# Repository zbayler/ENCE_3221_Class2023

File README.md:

# Kitchen Timer
Embedded Systems Programming;  
University of Denver, ENCE 3231

### Phase A: (guided)  
Designing and building a kitchen timer Arduino shield. 
- PCB design (but used provided physical version for the sake of time)
- Code development

### Phase B:  
Designing and building a kitchen timer.  
- Standalone PCB  
- 3D printing an enclosure

### Phase C: (incomplete)
STM32F407 Discovery Kit kitchen timer implementation. 

### Phase D: (all files included in separate folder) 
Final Project - Mini Lightsaber

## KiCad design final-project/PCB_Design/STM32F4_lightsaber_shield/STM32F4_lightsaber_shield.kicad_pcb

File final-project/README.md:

# Mini Lightsaber
Embedded Systems Programming;  
University of Denver, ENCE 3231

### Project Idea: 
Build a mini lightsaber using an IMU, LED, and speaker

### Project Requirements: 
- Design a PCB shield for the STM32F407G Discovery Board 
- Build and test a prototype circuit

### Components included: 
- GY-521 Inertial Measurement Unit
- 4 pin RGB LED
- Speaker (connected with aux cord) 
- USB to microUSB adapter

### Folder Structure: 
- Audio Files: lightsaber .wav files 
- Blad Design: designs for the mini blade 
- Hardware Documents: datasheets and other documentation 
- Notes: pictures, videos, presentations, etc. 
- PCB Design: the kiCAD folder as well as gerber, schematics, BOM, etc. 
- STM32 Code: all programs used to test components and build the system 

### Status/Summary:   
Followed "Mutex Embedded" tutorials on youtube to help set up the IMU and play audio files.
IMU and LED test were successful and were successfully tested together (video in notes).
No luck playing an audio file from the USB drive and so no build has combined all three functions yet.

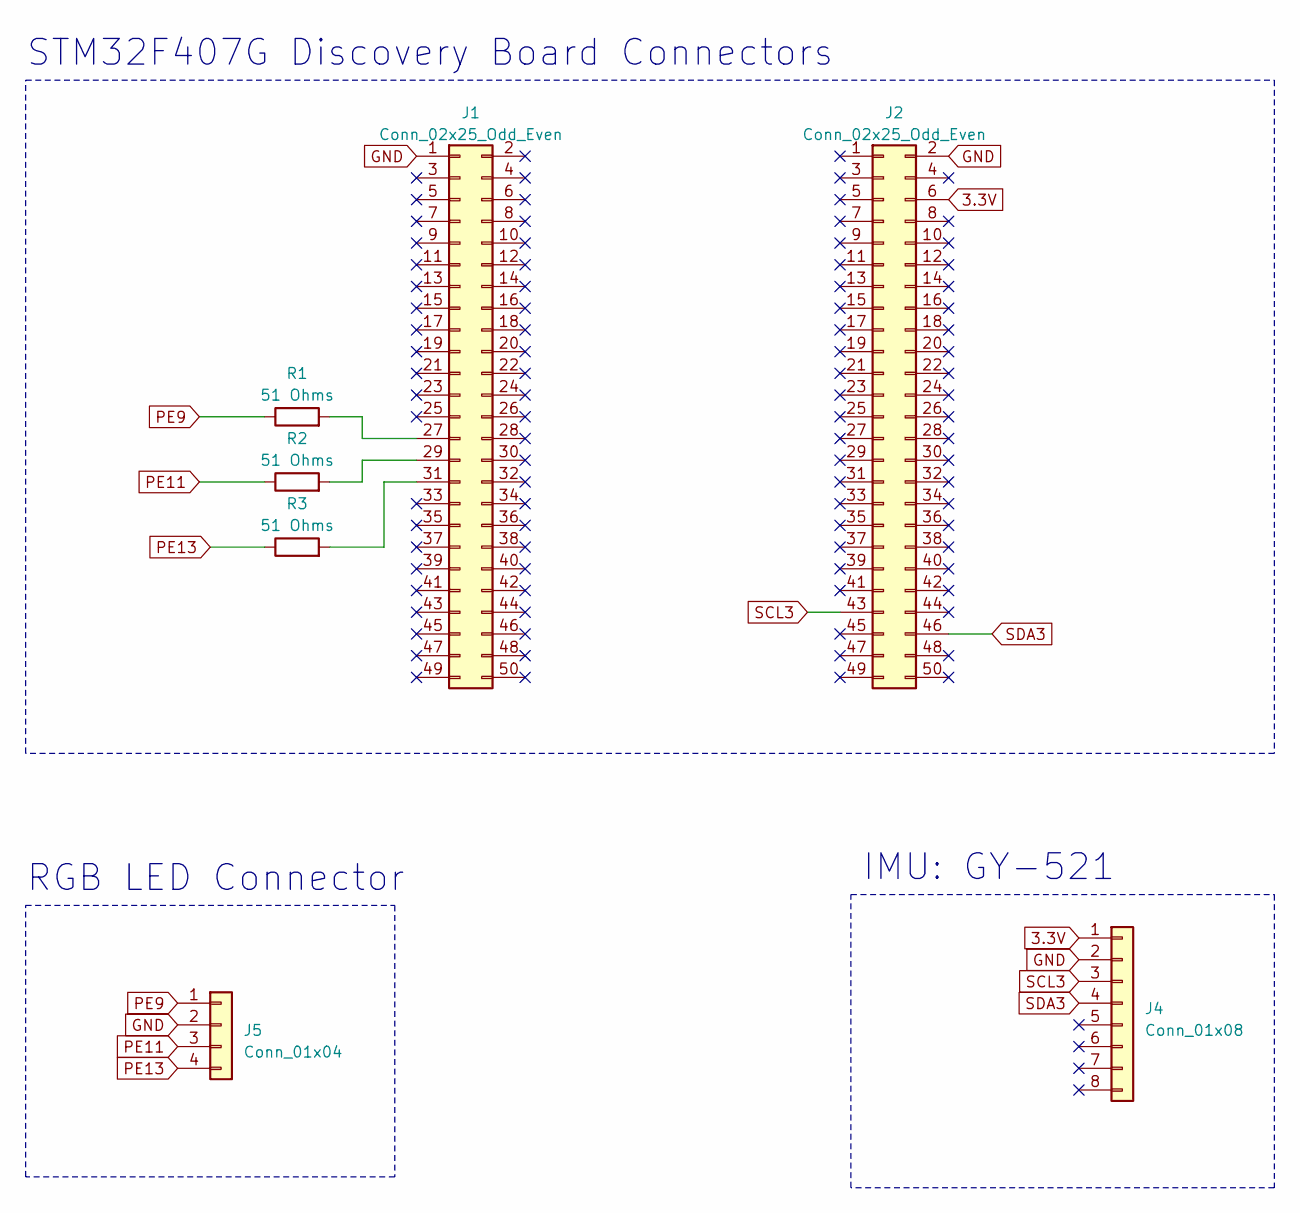
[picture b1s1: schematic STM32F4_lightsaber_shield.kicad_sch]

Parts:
J1, J2: Conn_02x25_Odd_Even; PinSocket_2x25_P1.27mm_Vertical
J4: Conn_01x08; PinSocket_1x08_P1.27mm_Vertical
J5: Conn_01x04; PinSocket_1x04_P1.27mm_Vertical
R1, R2, R3: 51 Ohms; R_0805_2012Metric

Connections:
3.3V: J2.6, J4.1
GND: J1.1, J2.2, J4.2, J5.2
unnamed: J1.27, R1.2
unnamed: J1.29, R2.2
unnamed: J1.31, R3.2
PE9: J5.1, R1.1
PE11: J5.3, R2.1
PE13: J5.4, R3.1
SCL3: J2.43, J4.3
SDA3: J2.46, J4.4

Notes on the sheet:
IMU: GY-521
RGB LED Connector
STM32F407G Discovery Board Connectors

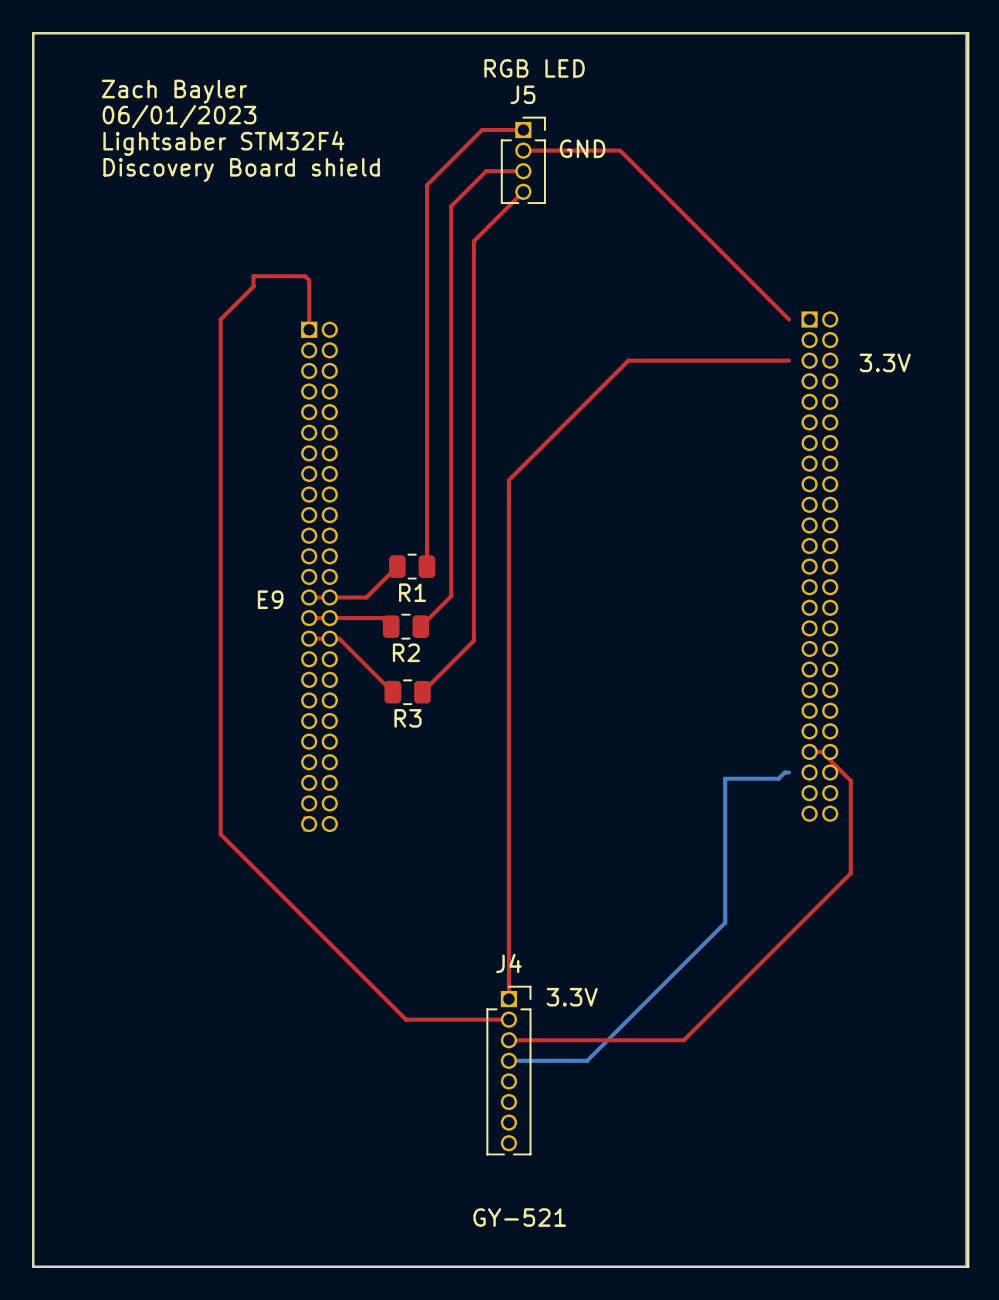
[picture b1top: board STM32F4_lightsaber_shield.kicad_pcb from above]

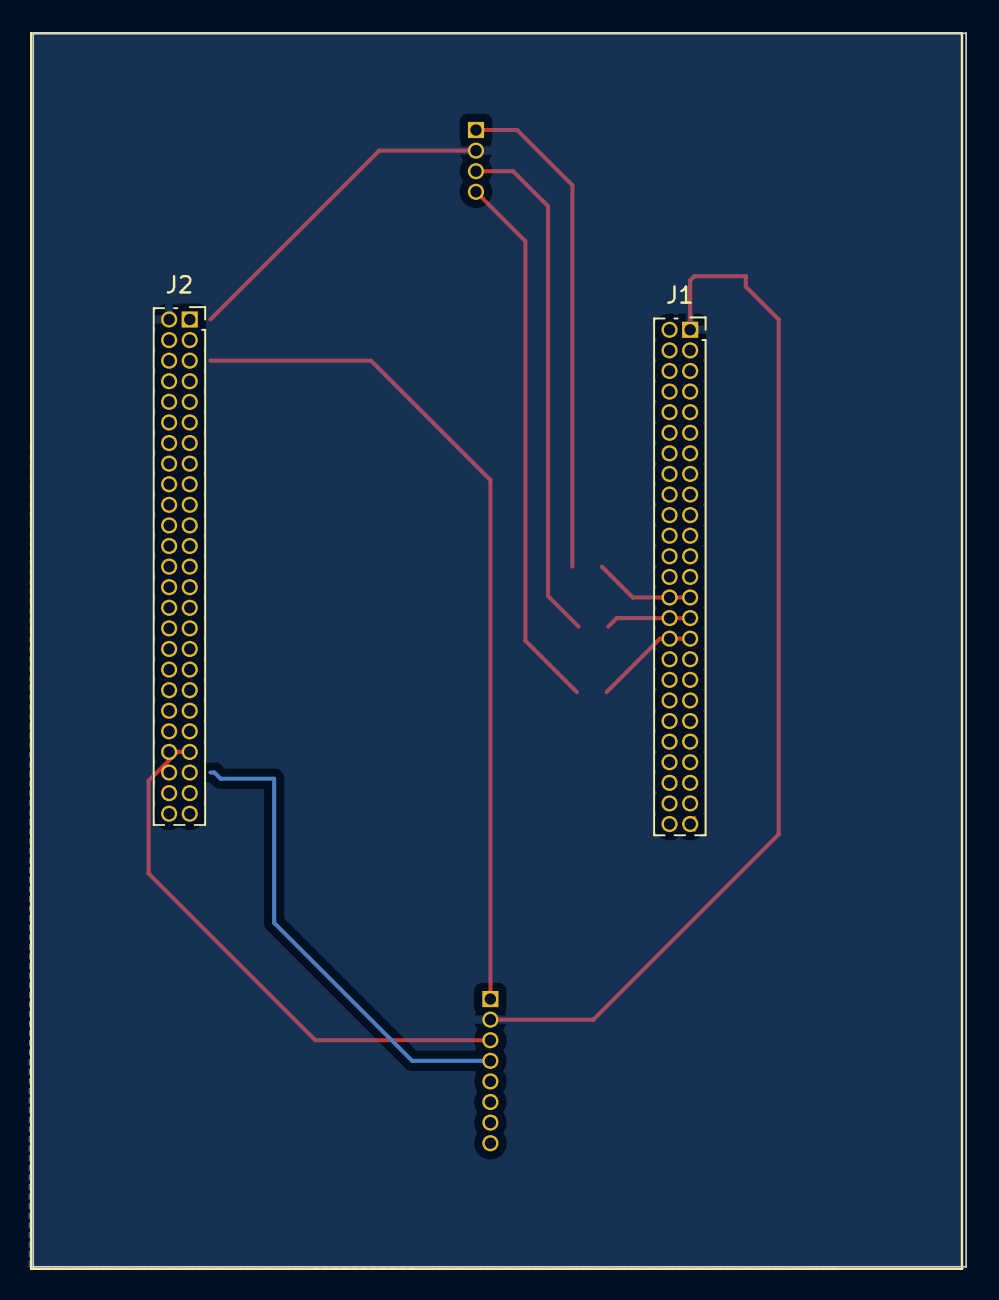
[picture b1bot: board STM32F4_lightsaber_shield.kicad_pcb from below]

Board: 2 copper layers, 57.5 x 76.1 mm, 7 parts (2 on the bottom side), 10 nets.

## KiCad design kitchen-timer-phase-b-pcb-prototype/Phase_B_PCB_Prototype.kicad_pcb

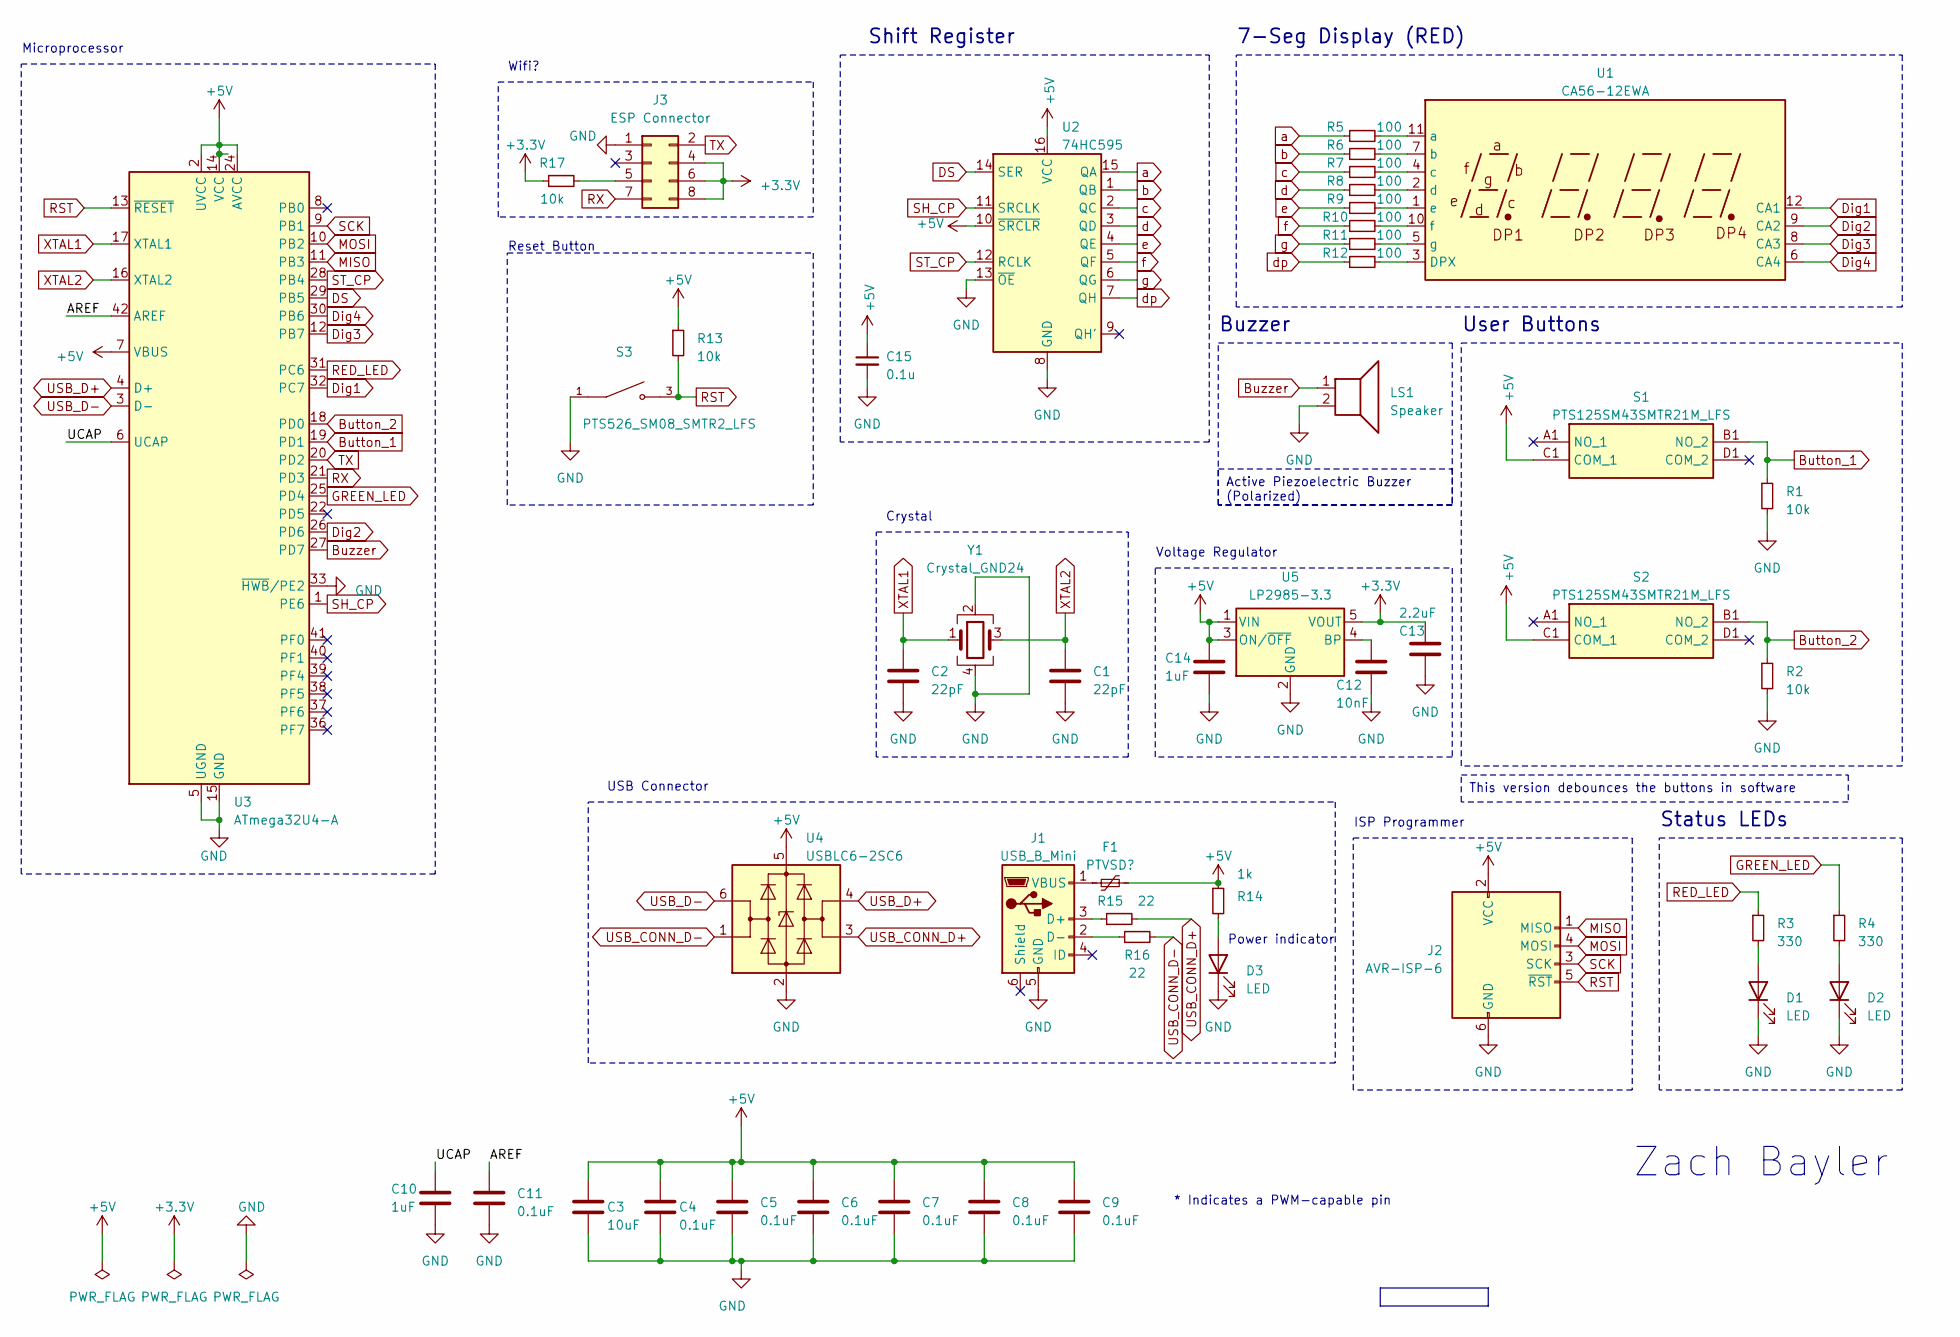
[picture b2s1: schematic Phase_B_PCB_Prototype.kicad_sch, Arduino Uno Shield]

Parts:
C1, C2: 22pF; C_0603_1608Metric
C3: 10uF; C_0603_1608Metric
C4, C5, C6, C7, C8, C9, C11: 0.1uF; C_0603_1608Metric
C10, C14: 1uF; C_0603_1608Metric
C12: 10nF; C_0603_1608Metric
C13: 2.2uF; C_0603_1608Metric
C15: 0.1u; C_0603_1608Metric
D1, D2, D3: LED; LED_0805_2012Metric
F1: PTVSD?; Fuse_1812_4532Metric
J1: USB_B_Mini; USB_Mini-B_Lumberg_2486_01_Horizontal
J2: AVR-ISP-6; PinSocket_2x03_P2.54mm_Vertical
J3: ESP Connector; PinSocket_2x04_P2.54mm_Vertical
LS1: Speaker; Buzzer_12x9.5RM7.6
R1, R2, R13, R17: 10k; R_0603_1608Metric
R3, R4: 330; R_0805_2012Metric
R5, R6, R7, R8, R9, R10, R11, R12: 100; R_0805_2012Metric
R14: 1k; R_0805_2012Metric
R15, R16: 22; R_0603_1608Metric
S1, S2: PTS125SM43SMTR21M_LFS; PTS125_SMD_Button; Manufacturer_Part_Number PTS125SM43SMTR21M LFS; Mouser Part Number 611-PTS125S43SMTRLFS
S3: PTS526_SM08_SMTR2_LFS; PTS526_SMD_Button; PARTREV 20 mar 19
U1: CA56-12EWA
U2: 74HC595; TSSOP-16_4.4x5mm_P0.65mm
U3: ATmega32U4-A; TQFP-44_10x10mm_P0.8mm
U4: USBLC6-2SC6; SOT-23-6
U5: LP2985-3.3; SOT-23-5
Y1: Crystal_GND24; Crystal_SMD_Abracon_ABM8G-4Pin_3.2x2.5mm

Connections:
+3.3V: C13.1, J3.4, J3.6, J3.8, R17.1, U5.5 (VOUT)
+5V: C3.1, C4.1, C5.1, C6.1, C7.1, C8.1, C9.1, C14.1, C15.1, F1.2, J2.2 (VCC), R13.1, R14.1, S1.C1 (COM_1), S2.C1 (COM_1), U2.10 (~SRCLR), U2.16 (VCC), U3.2 (UVCC), U3.7 (VBUS), U3.14 (VCC), U3.24 (AVCC), U3.34 (VCC), U3.44 (AVCC), U4.5 (VBUS), U5.1 (VIN), U5.3 (ON/~OFF)
/AREF: C11.1, U3.42 (AREF)
/UCAP: C10.1, U3.6 (UCAP)
Button_1: R1.1, S1.B1 (NO_2), U3.19 (PD1)
Button_2: R2.1, S2.B1 (NO_2), U3.18 (PD0)
Buzzer: LS1.1, U3.27 (PD7)
DS: U2.14 (SER), U3.29 (PB5)
Dig1: U1.12 (CA1), U3.32 (PC7)
Dig2: U1.9 (CA2), U3.26 (PD6)
Dig3: U1.8 (CA3), U3.12 (PB7)
Dig4: U1.6 (CA4), U3.30 (PB6)
GND: C1.2, C2.2, C3.2, C4.2, C5.2, C6.2, C7.2, C8.2, C9.2, C10.2, C11.2, C12.2, C13.2, C14.2, C15.2, D1.1 (K), D2.1 (K), D3.1 (K), J1.5 (GND), J2.6 (GND), J3.1, LS1.2, R1.2, R2.2, S3.1, U2.8 (GND), U2.13 (~OE), U3.5 (UGND), U3.15 (GND), U3.23 (GND), U3.33 (~HWB/PE2), U3.35 (GND), U3.43 (GND), U4.2 (GND), U5.2 (GND), Y1.2, Y1.4
GREEN_LED: R4.1, U3.25 (PD4)
MISO: J2.1 (MISO), U3.11 (PB3)
MOSI: J2.4 (MOSI), U3.10 (PB2)
unnamed: D1.2 (A), R3.2
unnamed: D2.2 (A), R4.2
unnamed: D3.2 (A), R14.2
unnamed: J1.3 (D+), R15.1
unnamed: J1.2 (D-), R16.1
unnamed: F1.1, J1.1 (VBUS)
unnamed: J3.5, R17.2
unnamed: R12.2, U1.3 (DPX)
unnamed: R5.2, U1.11 (a)
unnamed: R6.2, U1.7 (b)
unnamed: R7.2, U1.4 (c)
unnamed: R8.2, U1.2 (d)
unnamed: R9.2, U1.1 (e)
unnamed: R10.2, U1.10 (f)
unnamed: R11.2, U1.5 (g)
unnamed: C12.1, U5.4 (BP)
RED_LED: R3.1, U3.31 (PC6)
RST: J2.5 (~RST), R13.2, S3.3, U3.13 (~RESET)
RX: J3.7, U3.21 (PD3)
SCK: J2.3 (SCK), U3.9 (PB1)
SH_CP: U2.11 (SRCLK), U3.1 (PE6)
ST_CP: U2.12 (RCLK), U3.28 (PB4)
TX: J3.2, U3.20 (PD2)
USB_CONN_D+: R15.2, U4.3 (I/O2)
USB_CONN_D-: R16.2, U4.1 (I/O1)
USB_D+: U3.4 (D+), U4.4 (I/O2)
USB_D-: U3.3 (D-), U4.6 (I/O1)
XTAL1: C2.1, U3.17 (XTAL1), Y1.1
XTAL2: C1.1, U3.16 (XTAL2), Y1.3
a: R5.1, U2.15 (QA)
b: R6.1, U2.1 (QB)
c: R7.1, U2.2 (QC)
d: R8.1, U2.3 (QD)
dp: R12.1, U2.7 (QH)
e: R9.1, U2.4 (QE)
f: R10.1, U2.5 (QF)
g: R11.1, U2.6 (QG)

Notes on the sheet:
Active Piezoelectric Buzzer (Polarized)
This version debounces the buttons in software
Reset Button
Shift Register
Zach Bayler
Microprocessor
USB Connector
ISP Programmer
Status LEDs
Wifi?
Power indicator
User Buttons
Buzzer
* Indicates a PWM-capable pin
Voltage Regulator
7-Seg Display (RED)
Crystal

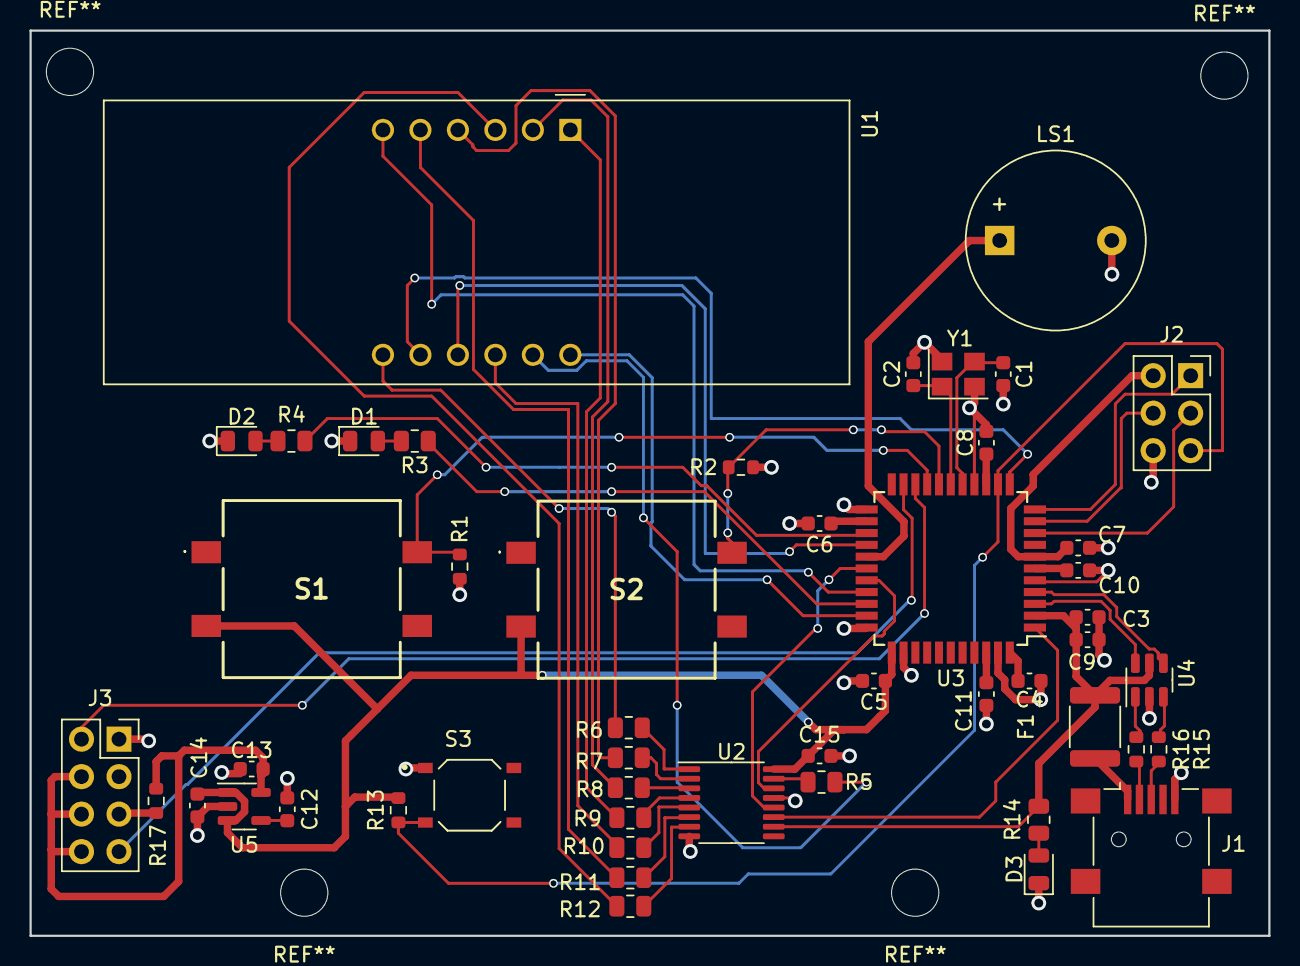
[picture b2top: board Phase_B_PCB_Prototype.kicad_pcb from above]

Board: 2 copper layers, 83.9 x 61.3 mm, 49 parts (0 on the bottom side), 53 nets.

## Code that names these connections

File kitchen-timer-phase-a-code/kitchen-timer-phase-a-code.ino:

// Zach Bayler
// Embedded Systems Programming
// 04/13/2023
// Developed with help from Dr. Martins' provided resources

/*
Kitchen Timer
- start/stop button
- increment seconds button (add to time left)
- display seconds left
- both LEDs on = stopped
- green LED on = running
- red only = alarm (reached 0)
*/

// Pin assignments
#define BUTTON_1  2
#define BUTTON_2  3
#define GREEN_LED 4
#define RED_LED   5
#define BUZZER 6

#define DATA      9   //74HC595  pin 8 DS
#define LATCH     8   //74HC595  pin 9 STCP
#define CLOCK     7  //74HC595  pin 10 SHCP

#define DIGIT_4   10
#define DIGIT_3   11
#define DIGIT_2   12
#define DIGIT_1   13

// time between displaying digits on the 7 segment display in ms 
// (have to rotate quickly between them)
#define digitDelay 3

// segment assignments to display correct digit on 7-segment (0-9,a-f)
unsigned char gTable[]=
{0x3f,0x06,0x5b,0x4f,0x66,0x6d,0x7d,0x07,0x7f,0x6f,0x77,0x7c
,0x39,0x5e,0x79,0x71,0x00};

//volatile variables
volatile unsigned int gTimeLeftSeconds = 30;
volatile int gButtonFlag2 = 0;

//governing state variable
// 0 is paused, 1 is counting down, 2 = alarm (hit 0s)
uint8_t gState = 0; 


unsigned int gReloadTimer1 = 62500; // corresponds to 1 second


void setup() {
  // LEDs Pins
  pinMode(RED_LED, OUTPUT);
  pinMode(GREEN_LED, OUTPUT);

  // Button Pins
  pinMode(BUTTON_1, INPUT_PULLUP);
  attachInterrupt(digitalPinToInterrupt(BUTTON_1), Button_1_ISR, RISING);
  pinMode(BUTTON_2, INPUT_PULLUP);
  attachInterrupt(digitalPinToInterrupt(BUTTON_2), Button_2_ISR, RISING);

  // Buzzer Pin
  pinMode(BUZZER, OUTPUT);

  // 7-Seg Display
  pinMode(DIGIT_1, OUTPUT);
  pinMode(DIGIT_2, OUTPUT);
  pinMode(DIGIT_3, OUTPUT);
  pinMode(DIGIT_4, OUTPUT);

  // Shift Register Pins
  pinMode(LATCH, OUTPUT);
  pinMode(CLOCK, OUTPUT);
  pinMode(DATA, OUTPUT);

  //setup timer 1
  noInterrupts();
  TCCR1A = 0;
  TCCR1B = 0;
  OCR1A = gReloadTimer1; // compare match register 16MHz/256
  TCCR1B |= (1<<WGM12);   // CTC mode 
  TIMSK1 |= (1<<OCIE1A);  // enable timer compare interrupt
  interrupts();

}


// increment time left 
void Button_1_ISR()
{
  for(int i = 0; i<30000; i++);    //software debounce; needs bigger but couldn't use bigger because that messes with the behavior
  gTimeLeftSeconds++;
}

// start/stop button
void Button_2_ISR()
{ 
  for(int i = 0; i<30000; i++);     //software debounce
  gButtonFlag2++;
  if((gButtonFlag2 % 2) == 0){      //alternates between states on press
    gState = 0;
  }
  else{
    gState = 1;
  }
  
}


// Write multiple digits to the 4x7-segment display at the "same time"
// digit1 is the left most place (MSB)
void write_display(int digit1, int digit2, int digit3, int digit4){

  //turn all digits off
  digitalWrite(DIGIT_1, HIGH);
  digitalWrite(DIGIT_2, HIGH);
  digitalWrite(DIGIT_3, HIGH);
  digitalWrite(DIGIT_4, HIGH);

  //write first digit with given parameter
  digitalWrite(LATCH, LOW);
  shiftOut(DATA, CLOCK, MSBFIRST, gTable[digit1]);
  digitalWrite(LATCH, HIGH);
  digitalWrite(DIGIT_1, LOW);
  delay(digitDelay);              //hold on for a brief period
  digitalWrite(DIGIT_1, HIGH);    //turn off

  digitalWrite(LATCH, LOW);
  shiftOut(DATA, CLOCK, MSBFIRST, gTable[digit2] | (1<<7));   //include decimal point after 2nd MSB
  digitalWrite(LATCH, HIGH);
  digitalWrite(DIGIT_2, LOW);
  delay(digitDelay);
  digitalWrite(DIGIT_2, HIGH);

  digitalWrite(LATCH, LOW);
  shiftOut(DATA, CLOCK, MSBFIRST, gTable[digit3]);
  digitalWrite(LATCH, HIGH);
  digitalWrite(DIGIT_3, LOW);
  delay(digitDelay);
  digitalWrite(DIGIT_3, HIGH);


  digitalWrite(LATCH, LOW);
  shiftOut(DATA, CLOCK, MSBFIRST, gTable[digit4]);
  digitalWrite(LATCH, HIGH);
  digitalWrite(DIGIT_4, LOW);
  delay(digitDelay);
  digitalWrite(DIGIT_4, HIGH);
}

//converts time in seconds to minutes and seconds then calls write function
void display(int timeSeconds){

  int digit_4 = (int) timeSeconds % 10;            //seconds; ones place xx:x0
  int digit_3 = (int) (timeSeconds / 10) % 6;      //seconds; tens place xx:0x
  int digit_2 = (int) (timeSeconds / 60) % 10;     //minutes; ones place x0:xx
  int digit_1 = (int) (timeSeconds / 600) % 6;     //minutes; tens place 0x:xx

  write_display(digit_1, digit_2, digit_3, digit_4);
}

// Timer1 interrupt service routine (ISR)
ISR(TIMER1_COMPA_vect)  
{
  //decrement count once per second
  gTimeLeftSeconds--;

  // timer end condition
  if(gTimeLeftSeconds == 0)
  {
    gState = 2;
  }
}

void startTimer1()
{
  // Start Timer
  TCCR1B |= (1<<CS12);    // 256 prescaler 
  TIMSK1 |= (1<<OCIE1A);  // enable timer compare interrupt
}

void stopTimer1()
{
  // Stop Timer
  TCCR1B &= 0b11111000; // stop clock
  TIMSK1 = 0; // cancel clock timer interrupt
}

//turn on buzzer in a pattern
void activeBuzzer()
{
  unsigned char i;
  unsigned char sleepTime = 1; // ms
  
  for(i=0;i<100;i++)
  {
    digitalWrite(BUZZER,HIGH);
    delay(sleepTime);//wait for 1ms
    digitalWrite(BUZZER,LOW);
    delay(sleepTime);//wait for 1ms
  }
}

void loop() {

  //control LEDs and counting based on desired state
  switch(gState){
    
    //paused; both LEDs on
    case 0:
      stopTimer1();
      digitalWrite(RED_LED, HIGH);
      digitalWrite(GREEN_LED, HIGH);
      break;

    //running; red off, green on
    case 1:
      startTimer1();
      digitalWrite(RED_LED, LOW);
      digitalWrite(GREEN_LED, HIGH);
      break;

    //end alarm; red on, green off
    case 2:
      digitalWrite(RED_LED, HIGH);
      digitalWrite(GREEN_LED, LOW);
      activeBuzzer();
      break;
  }

  //show count down
  display(gTimeLeftSeconds);

}

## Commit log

2023-04-13 Create kitchen-timer-phase-a.ino
    Kitchen timer Arduino Uno shield code. Developed with help from Dr. Martins provided resources.
2023-04-13 Update README.md
    Updating repository to include all of the project phases.
2023-04-13 Renamed Code
2023-04-13 Created PCB design, flow chart, and report.
2023-04-18 PCB-layout-v1
2023-04-18 Phase B PCB Enclosure v1
2023-04-18 Reorganized and renamed some stuff
2023-04-19 Progressing on PCB layout
2023-04-20 PCB layout and routing
2023-04-20 Working on the enclosure
2023-04-20 Enclosure and PCB updates
2023-04-21 Finished PCB and created gerber files
2023-04-21 Deleted old pcb version
2023-04-24 Developing enclosure
2023-05-04 Major Reorganization and upload of Phase B
2023-06-02 final project upload
2023-06-07 reorganized and uploaded final phase b report
